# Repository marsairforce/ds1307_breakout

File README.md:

# A breakout module for a DS1307 Real Time Clock

## Why

Why would you build a module, that costs you more, than existing breakout modules you can readily buy, that do more things?  Well. to learn of course.
I also had some parts in stock from AliExpress. Felt kind of silly to go order some break out boards when I could just build me some.

I wanted a smaller footprint size than the modules that existed, working at the time to build a tiny clock for the kids. I ended up using the adafruit breakout because i had it already, but for next time I wanted to be smaller.  To do this I just didn't put the battery holder on the board, a pin to hook it up. So we have to provide our own battery. And I used components on both sides of the board.  I don't really like the not-surface mount crystal oscillator, but again just using up some stock I happened to have here.

Schematics done using Kicad

## Software

Just using one of the existing DS1307 libraries for your platform should work. I don't really have my own library for this yet, I use the Adafruit one for Arduino.

## Schematic

The KiCad project for schematic and PCB layout are here.

## Specs

* The [DS1307](doc/DS1307.pdf) Real-Time Clock IC ( I2C, 5V)

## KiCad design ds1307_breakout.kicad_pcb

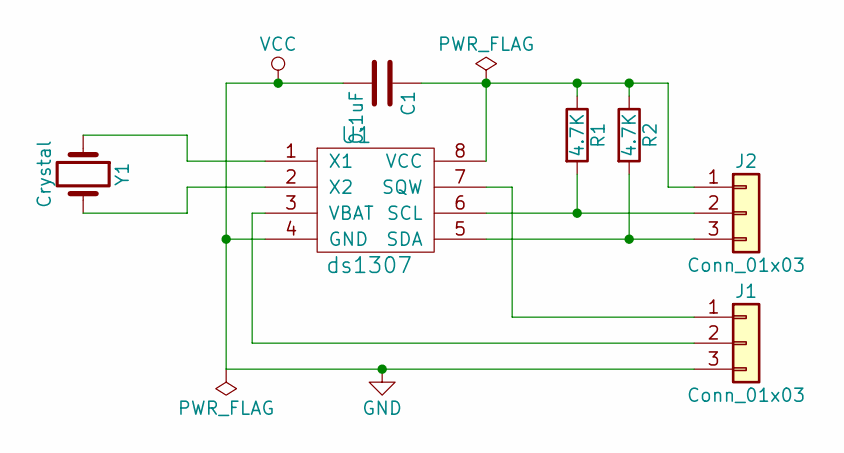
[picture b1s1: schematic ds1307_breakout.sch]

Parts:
C1: 0.1uF; C_0603
J1, J2: Conn_01x03; Pin_Header_Straight_1x03_Pitch2.54mm
R1, R2: 4.7K; R_0603
U1: ds1307; SOIC-8-1EP_3.9x4.9mm_Pitch1.27mm
Y1: Crystal; Crystal_DS26_d2.0mm_l6.0mm_Horizontal

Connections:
GND: C1.2, J1.3, U1.4 (GND)
unnamed: C1.1, J2.1, R1.1, R2.1, U1.8 (VCC)
unnamed: J1.1, U1.7 (SQW)
unnamed: J1.2, U1.3 (VBAT)
unnamed: J2.2, R1.2, U1.6 (SCL)
unnamed: J2.3, R2.2, U1.5 (SDA)
unnamed: U1.1 (X1), Y1.1
unnamed: U1.2 (X2), Y1.2

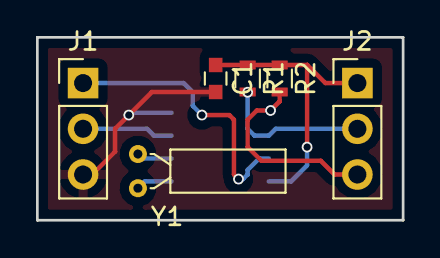
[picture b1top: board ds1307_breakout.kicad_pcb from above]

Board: 2 copper layers, 20.3 x 10.2 mm, 7 parts (1 on the bottom side), 8 nets.

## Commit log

2018-03-29 design a break out board for holding a 8-soic package DS1307 RTC
2018-05-01 add documentation
2019-11-20 update documentation
2019-11-20 add datasheet
